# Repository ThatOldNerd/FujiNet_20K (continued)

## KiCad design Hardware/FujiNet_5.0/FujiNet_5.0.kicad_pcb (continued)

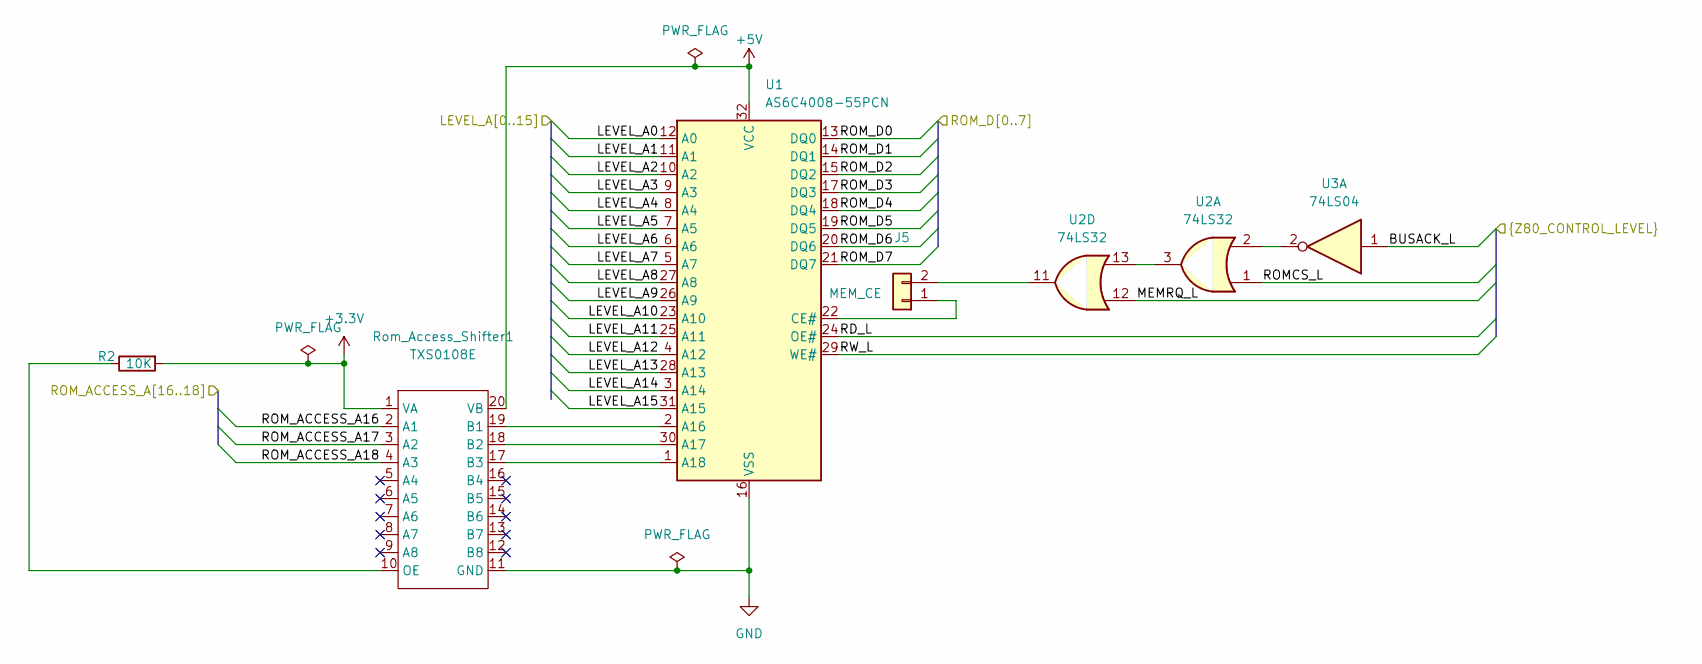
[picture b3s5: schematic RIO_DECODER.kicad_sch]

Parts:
J5: MEM_CE; PinHeader_1x02_P2.54mm_Vertical
R2: 10K; R_Axial_DIN0207_L6.3mm_D2.5mm_P10.16mm_Horizontal
Rom_Access_Shifter1: TXS0108E; Adafruit_TXB010_ breakout_board
U1: AS6C4008-55PCN; DIP-32_W15.24mm
U2: 74LS32; DIP-14_W7.62mm_Socket
U3: 74LS04; DIP-14_W7.62mm_Socket

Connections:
+3.3V: R2.2, Rom_Access_Shifter1.1 (VA); also elsewhere on the board
+5V: Rom_Access_Shifter1.20 (VB), U1.32 (VCC); also elsewhere on the board
/DATA FLOW CONTROL/BUSACK_L: U3.1; also elsewhere on the board
/DATA FLOW CONTROL/LEVEL_A0: U1.12 (A0); also elsewhere on the board
/DATA FLOW CONTROL/LEVEL_A1: U1.11 (A1); also elsewhere on the board
/DATA FLOW CONTROL/LEVEL_A2: U1.10 (A2); also elsewhere on the board
/DATA FLOW CONTROL/LEVEL_A3: U1.9 (A3); also elsewhere on the board
/DATA FLOW CONTROL/LEVEL_A4: U1.8 (A4); also elsewhere on the board
/DATA FLOW CONTROL/LEVEL_A5: U1.7 (A5); also elsewhere on the board
/DATA FLOW CONTROL/LEVEL_A6: U1.6 (A6); also elsewhere on the board
/DATA FLOW CONTROL/LEVEL_A7: U1.5 (A7); also elsewhere on the board
/DATA FLOW CONTROL/LEVEL_A8: U1.27 (A8); also elsewhere on the board
/DATA FLOW CONTROL/LEVEL_A9: U1.26 (A9); also elsewhere on the board
/DATA FLOW CONTROL/LEVEL_A10: U1.23 (A10); also elsewhere on the board
/DATA FLOW CONTROL/LEVEL_A11: U1.25 (A11); also elsewhere on the board
/DATA FLOW CONTROL/LEVEL_A12: U1.4 (A12); also elsewhere on the board
/DATA FLOW CONTROL/LEVEL_A13: U1.28 (A13); also elsewhere on the board
/DATA FLOW CONTROL/LEVEL_A14: U1.3 (A14); also elsewhere on the board
/DATA FLOW CONTROL/LEVEL_A15: U1.31 (A15); also elsewhere on the board
/DATA FLOW CONTROL/LEVEL_D0: U1.13 (DQ0); also elsewhere on the board
/DATA FLOW CONTROL/LEVEL_D1: U1.14 (DQ1); also elsewhere on the board
/DATA FLOW CONTROL/LEVEL_D2: U1.15 (DQ2); also elsewhere on the board
/DATA FLOW CONTROL/LEVEL_D3: U1.17 (DQ3); also elsewhere on the board
/DATA FLOW CONTROL/LEVEL_D4: U1.18 (DQ4); also elsewhere on the board
/DATA FLOW CONTROL/LEVEL_D5: U1.19 (DQ5); also elsewhere on the board
/DATA FLOW CONTROL/LEVEL_D6: U1.20 (DQ6); also elsewhere on the board
/DATA FLOW CONTROL/LEVEL_D7: U1.21 (DQ7); also elsewhere on the board
/DATA FLOW CONTROL/MEMRQ_L: U2.12; also elsewhere on the board
/DATA FLOW CONTROL/RD_L: U1.24 (OE#); also elsewhere on the board
/DATA FLOW CONTROL/ROMCS_L: U2.1; also elsewhere on the board
/DATA FLOW CONTROL/RW_L: U1.29 (WE#); also elsewhere on the board
/ESP-32 Module/ROM_ACCESS_A16: Rom_Access_Shifter1.2 (A1); also elsewhere on the board
/ESP-32 Module/ROM_ACCESS_A17: Rom_Access_Shifter1.3 (A2); also elsewhere on the board
/ESP-32 Module/ROM_ACCESS_A18: Rom_Access_Shifter1.4 (A3); also elsewhere on the board
GND: Rom_Access_Shifter1.11 (GND), U1.16 (VSS); also elsewhere on the board
unnamed: J5.1, U1.22 (CE#)
unnamed: J5.2, U2.11
unnamed: Rom_Access_Shifter1.19 (B1), U1.2 (A16)
unnamed: Rom_Access_Shifter1.18 (B2), U1.30 (A17)
unnamed: Rom_Access_Shifter1.17 (B3), U1.1 (A18)
unnamed: R2.1, Rom_Access_Shifter1.10 (OE)
unnamed: U2.2, U3.2
unnamed: U2.3, U2.13

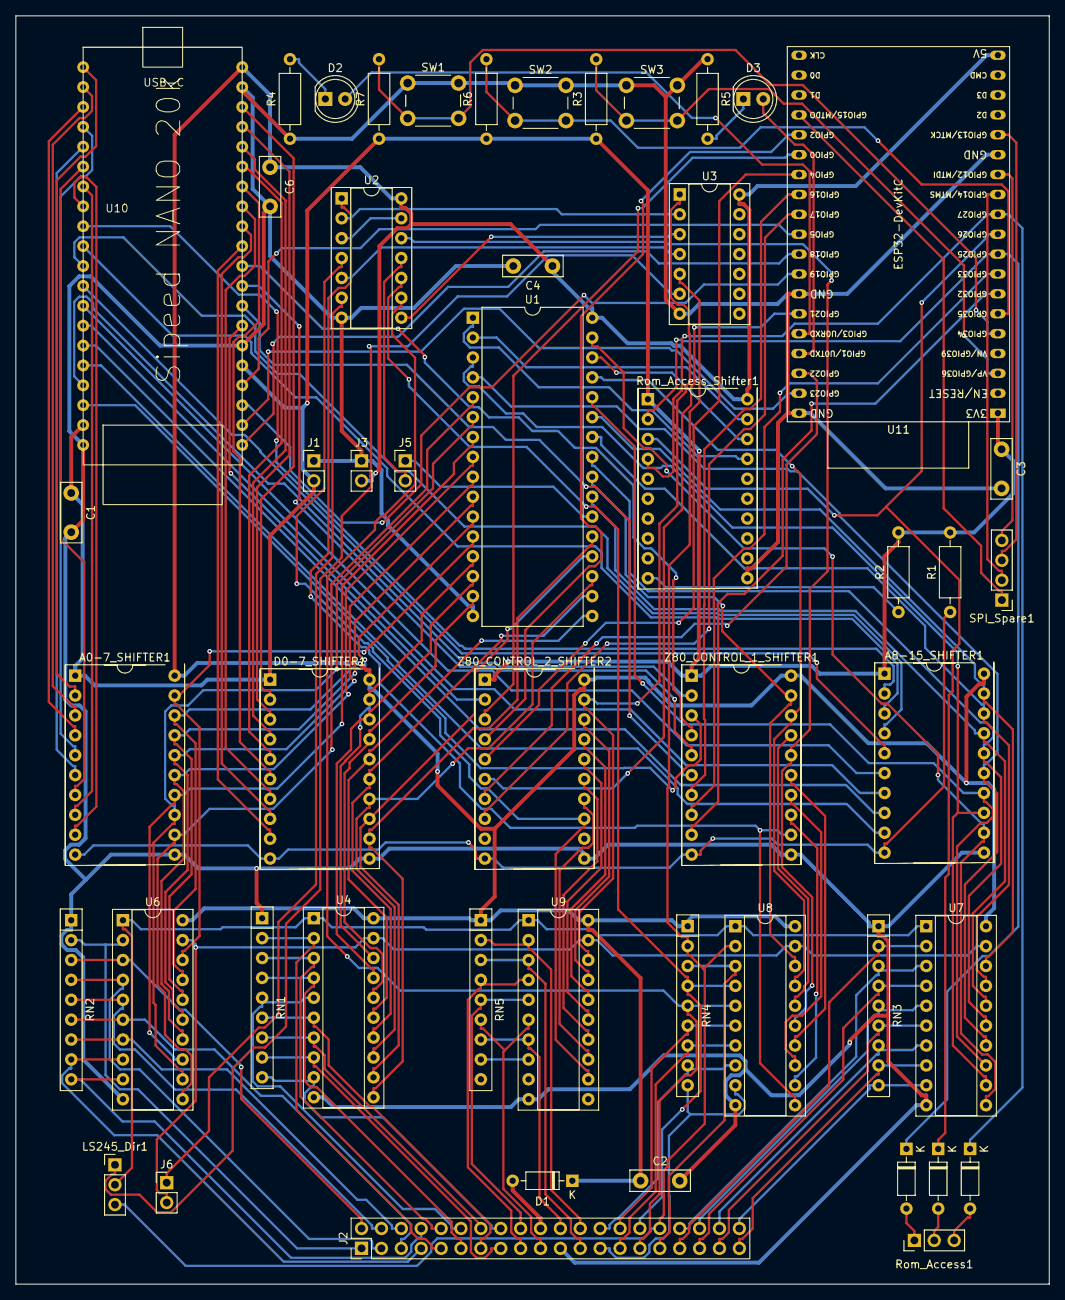
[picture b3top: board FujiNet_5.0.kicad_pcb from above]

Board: 2 copper layers, 132.0 x 162.0 mm, 50 parts (0 on the bottom side), 157 nets.
